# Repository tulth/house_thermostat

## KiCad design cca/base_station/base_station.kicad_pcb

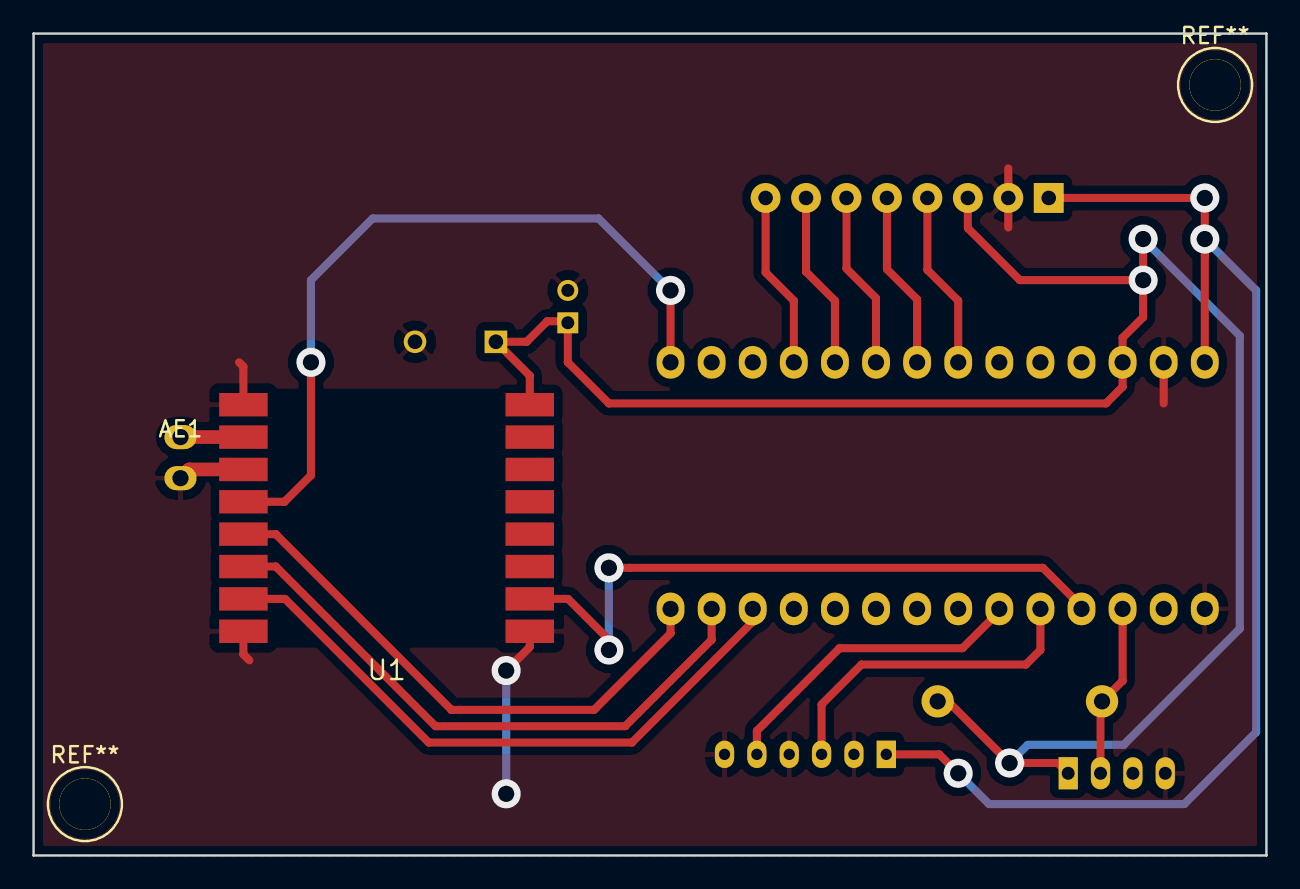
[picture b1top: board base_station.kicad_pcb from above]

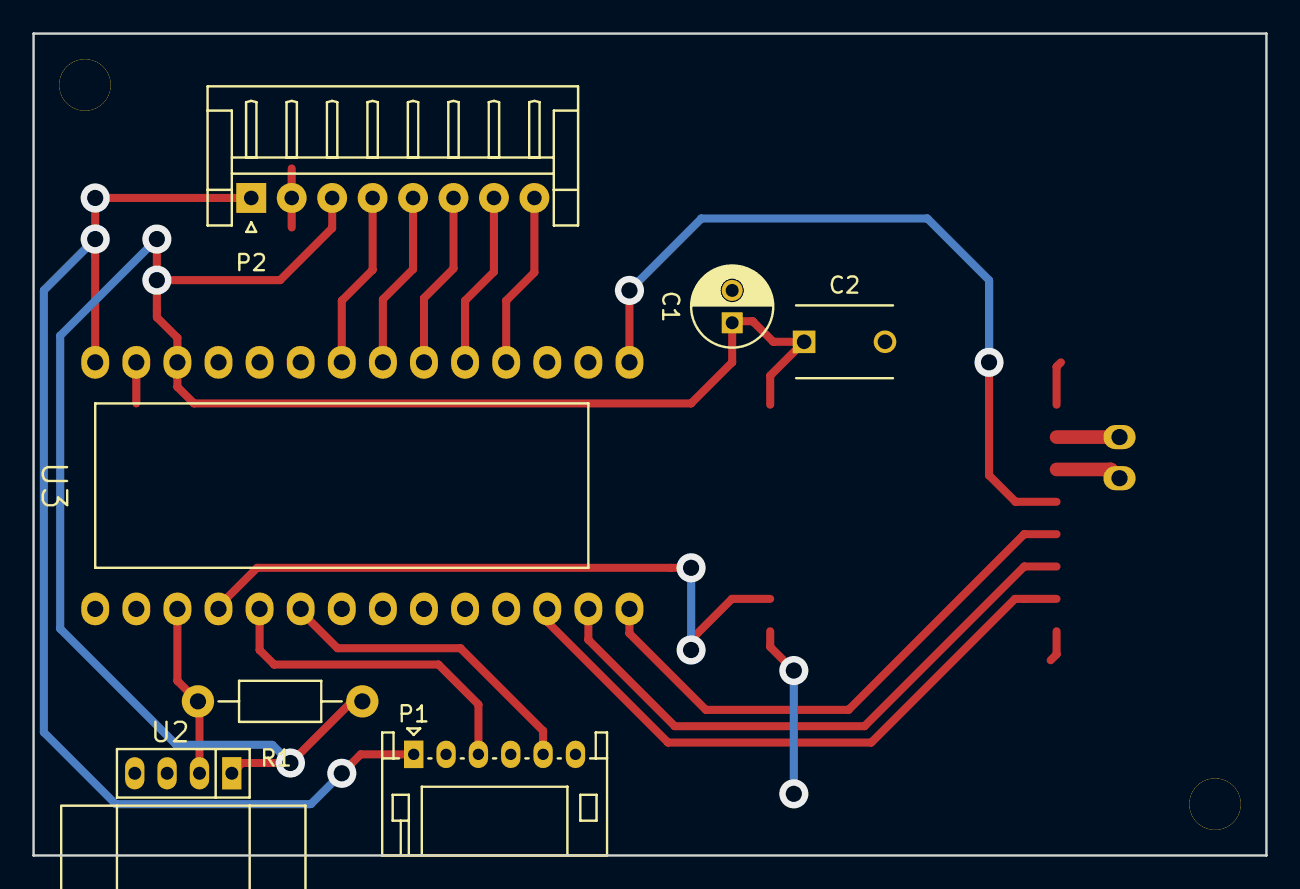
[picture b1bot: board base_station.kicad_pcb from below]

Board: 2 copper layers, 76.2 x 50.8 mm, 9 parts (7 on the bottom side), 17 nets.

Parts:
AE1: ANTENNA_915; ant_915_dipole_conn
C1: 10uF/16V; C_Radial_D5_L12.5_P2
C2: 0.1uF/50V; C_Disc_D6_P5
P1: tstat_ui_conn; JST_PH_RIGHT_6pin
P2: tstat_cable_con; JST_EH_RIGHT_8pin
R1: 4.75K; Resistor_Horizontal_RM10mm
U1: RFM69W
U2: DHT22
U3: TEENSY-LC; Teensy-3.2

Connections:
+3V3: C1.1, C2.1, P2.3, R1.1, U1.8, U2.1, U3.24
+5V: P1.1, P2.1, U3.26
GND: AE1.2, C1.2, C2.2, P1.2, P1.4, P1.6, P2.2, U1.1, U1.9, U1.11, U1.16, U2.4, U3.25, U3.27
unnamed: AE1.1, U1.10
unnamed: P1.3, U3.3
unnamed: P1.5, U3.4
unnamed: P2.4, U3.20
unnamed: P2.5, U3.19
unnamed: P2.6, U3.18
unnamed: P2.7, U3.17
unnamed: P2.8, U3.16
unnamed: R1.2, U2.2, U3.1
unnamed: U1.2, U3.2
unnamed: U1.12, U3.13
unnamed: U1.13, U3.12
unnamed: U1.14, U3.11
unnamed: U1.15, U3.10

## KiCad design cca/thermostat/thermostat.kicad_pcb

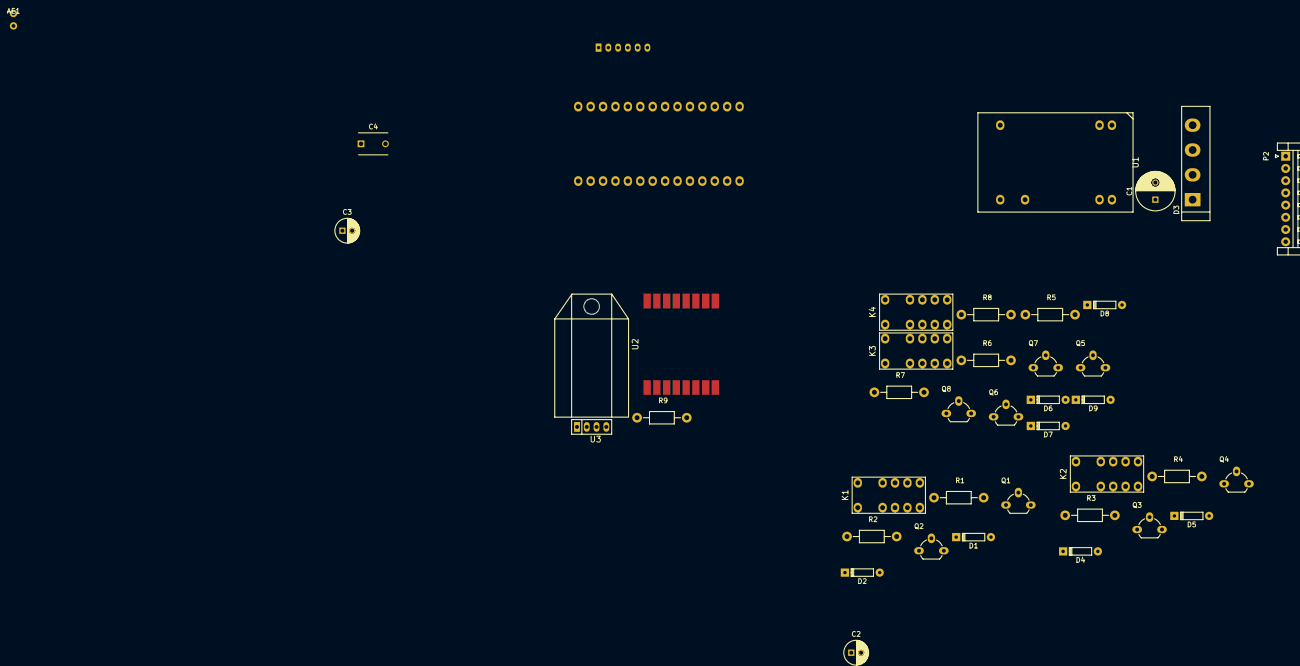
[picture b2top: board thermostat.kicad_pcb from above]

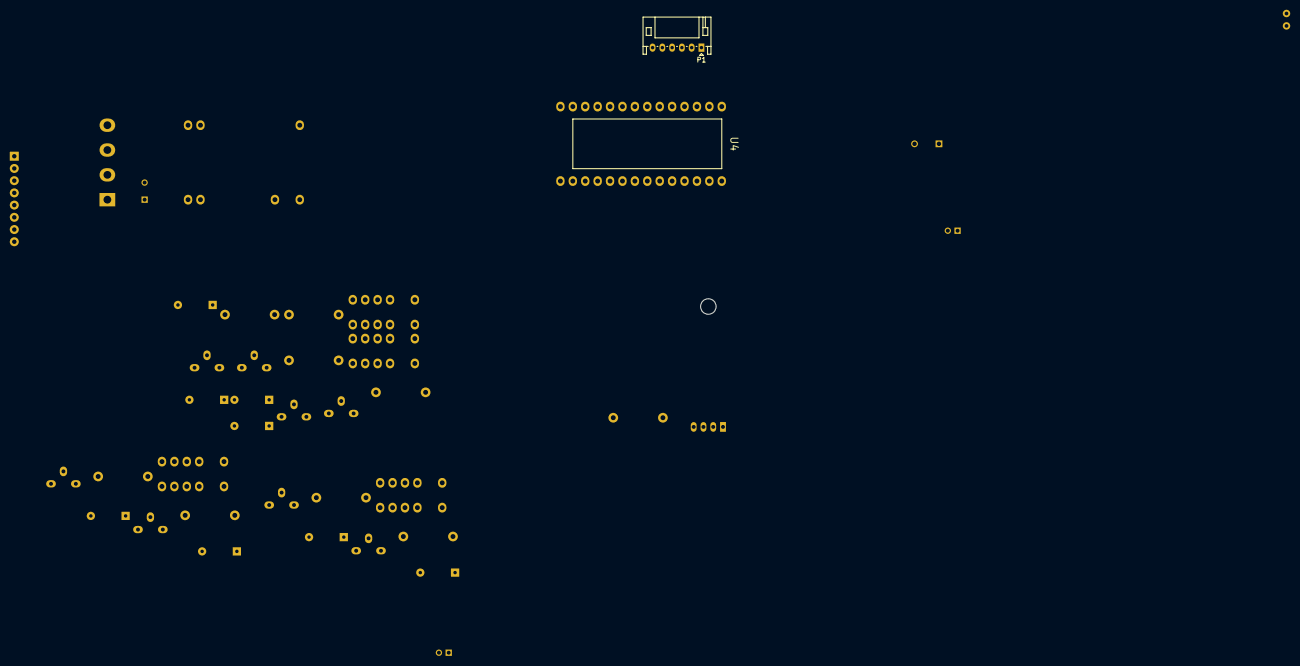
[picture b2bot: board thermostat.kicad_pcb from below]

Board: 2 copper layers, 41 parts (2 on the bottom side), 47 nets, no tracks yet.

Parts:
AE1: ANTENNA_915; ant_915_dipole_conn
C1: 47uF/63V; C_Radial_D8_L15_P3.5
C2, C3: 10uF/16V; C_Radial_D5_L12.5_P2
C4: 0.1uF/50V; C_Disc_D6_P5
D1, D2, D4, D5, D6, D7, D8, D9: 1N4148; DO-35
D3: GBU806; GBU
K1, K2, K3, K4: TX2-LT-5V-TH; RELAY_2_FORM_C
P1: tstat_ui_conn; JST_PH_RIGHT_6pin
P2: tstat_cable_con; JST_EH_RIGHT_8pin
Q1, Q2, Q3, Q4, Q5, Q6, Q7, Q8: 2N3904; TO-92_Molded_Wide_Oval
R1, R2: 4.75k; Resistor_Horizontal_RM10mm
R3, R4, R5, R6, R7, R8, R9: 4.75K; Resistor_Horizontal_RM10mm
U1: DJ06S4805A
U2: RFM69W
U3: DHT22
U4: TEENSY-LC; Teensy-3.2

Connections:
+3V3: C3.1, C4.1, R9.1, U2.8, U3.1, U4.24
+5V: C2.1, D1.1, D2.1, D4.1, D5.1, D6.1, D7.1, D8.1, D9.1, K1.1, K1.6, K2.1, K2.6, K3.7, K3.12, K4.7, K4.12, P1.1, U1.14, U4.26
/control_comm/ant: AE1.1, U2.10
/control_comm/coolMode: R6.1, U4.19
/control_comm/heatMode: R8.2, U4.18
/control_comm/idleMode: R5.1, U4.20
/control_comm/miso: U2.13, U4.12
/control_comm/mosi: U2.14, U4.11
/control_comm/nss: U2.15, U4.10
/control_comm/rfm_int: U2.2, U4.0
/control_comm/runMode: R7.2, U4.21
/control_comm/sck: U2.12, U4.13
/control_comm/ui_rx: P1.5, U4.4
/control_comm/ui_tx: P1.3, U4.3
/fan_off_uc: R2.2, U4.22
/fan_on_uc: R1.1, U4.23
/power/24VAC_1: D3.3, K1.4, K2.4, K3.9, K4.9, P2.1
/power/24VAC_2: D3.2, P2.2
/relay_emheat/E: K2.5, P2.8
/relay_emheat/RST: R4.2, U4.16
/relay_emheat/SET: R3.1, U4.17
/relay_fan/G: K1.5, P2.3
/relay_heatcool/B: K4.8, P2.6
/relay_heatcool/O: K4.10, P2.7
/relay_heatcool/W: K4.5, P2.5
/relay_heatcool/Y: K4.3, P2.4
GND: AE1.2, C2.2, C3.2, C4.2, P1.2, P1.4, P1.6, Q1.1, Q2.1, Q3.1, Q4.1, Q5.1, Q6.1, Q7.1, Q8.1, U1.16, U2.1, U2.9, U2.11, U2.16, U3.4, U4.25, U4.27
unnamed: C1.1, D3.1, U1.22, U1.23
unnamed: C1.2, D3.4, U1.2, U1.3
unnamed: D1.2, K1.7, Q1.3
unnamed: D2.2, K1.12, Q2.3
unnamed: D4.2, K2.7, Q3.3
unnamed: D5.2, K2.12, Q4.3
unnamed: D6.2, K3.1, Q5.3
unnamed: D7.2, K4.1, Q6.3
unnamed: D8.2, K3.6, Q7.3
unnamed: D9.2, K4.6, Q8.3
unnamed: K3.8, K4.4
unnamed: Q1.2, R1.2
unnamed: Q2.2, R2.1
unnamed: Q3.2, R3.2
unnamed: Q4.2, R4.1
unnamed: Q5.2, R5.2
unnamed: Q6.2, R6.2
unnamed: Q7.2, R7.1
unnamed: Q8.2, R8.1
unnamed: R9.2, U3.2, U4.1

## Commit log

2016-08-15 add kicad_common submodule, prelim thermostat schematic
2016-08-19 Prelim schem. TODO: battery backup, layout
2016-08-19 cleanup: delete unused sch pages
2016-08-19 cap cleanup pass, fully qualify footprints
2016-08-19 cleanup pass after clean checkout
2016-09-03 Pull in common lib changes
2016-09-03 Add rfm69w base station cca (also probably garage door opener schem)
2016-09-03 thermostat... wip many updates
2016-09-03 igore pcb report files
2016-09-03 set unused teensy pins as noconnects
2016-09-03 footprint drillholes metric
2016-09-03 footprint drillholes metric pt 2
2016-09-18 ignore *.net files for cca
2016-09-18 fix thermostat git ignore
2016-09-18 0.5mm fab pass
2016-09-18 Document flatcam steps as they can be fairly involved
2016-09-18 Cleanup flatcam readme
2016-09-18 updated wire holes and antenna to be 1.0mm drill. Added missing 3.3V optional e-point
2016-09-20 Moved rfm69w interrupt (dio0) to pin 2 of teensy-lc because pin 0 cannot function as an interrupt.
2016-09-22 just added a basic blink that builds for teensy-lc. Next up: add rfm69 lib.
2016-09-24 Add RFM69 submodule
2016-09-24 Add arduino SPI library.
2016-09-24 RFM69 update
2016-09-24 Update teensy submodule
2016-09-24 Build some rfm examples
